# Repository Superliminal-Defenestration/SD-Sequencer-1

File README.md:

Drum machine / sequencer being developed in Kicad 8. Open source and free to use, based mainly on Roland TR808s, etc.
As simple as it gets--- nothing to produce fancy attack/decay envelopes on most stuff, mostly only fancy VCA envelopes for white-noise based sounds. This is meant to be as easy to understand and low-cost as possible.
I'll be writing in notes as I develop the system on what math I'm using to determine components :).

White noise generation with transistor breakdown accredited to Moritz Klein!

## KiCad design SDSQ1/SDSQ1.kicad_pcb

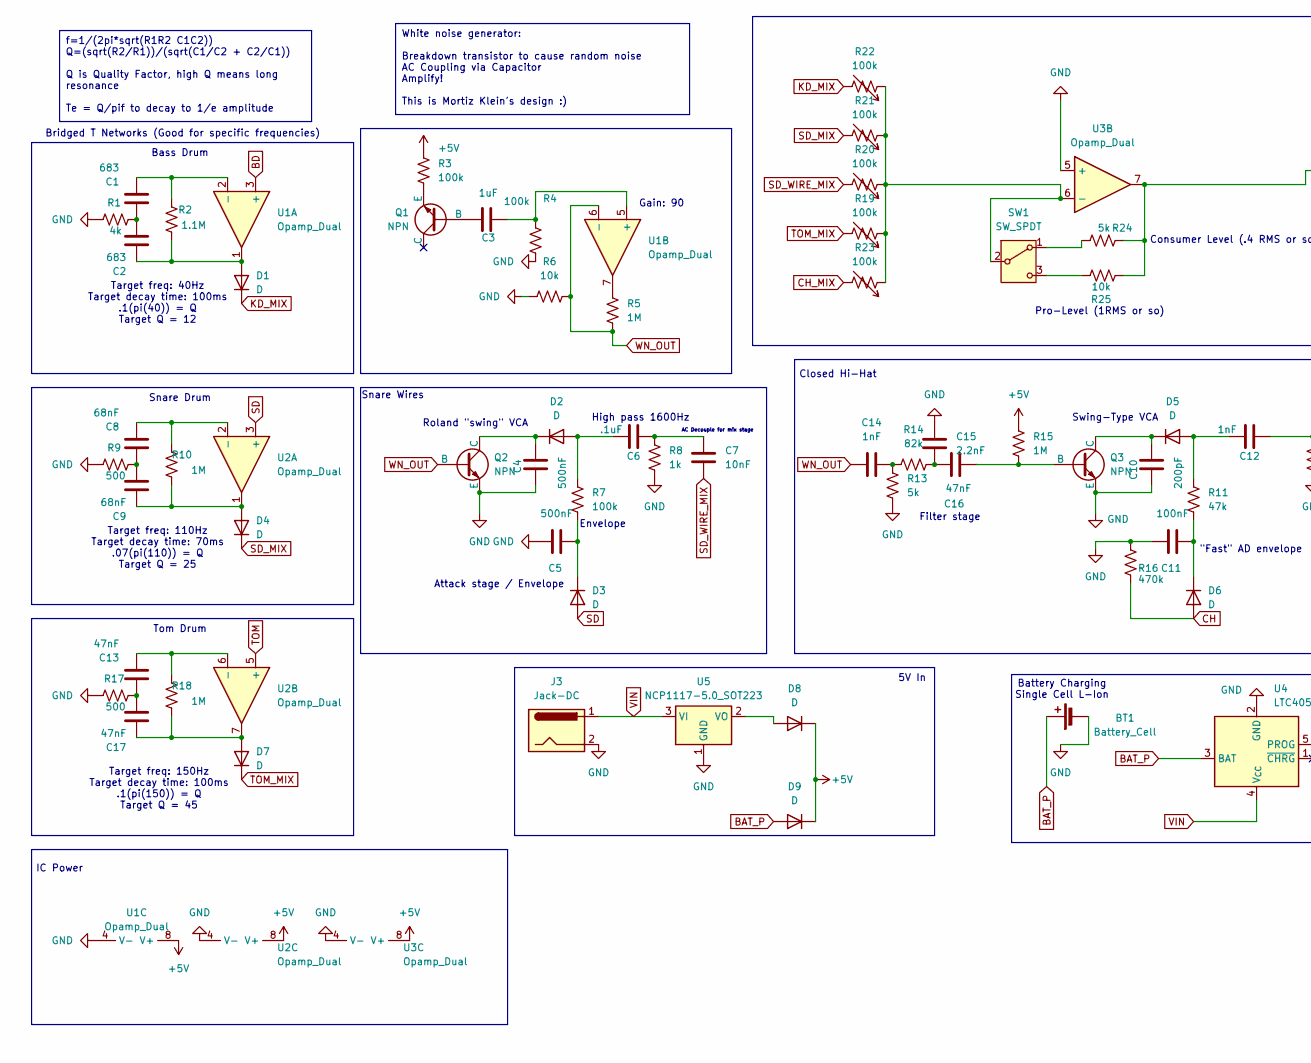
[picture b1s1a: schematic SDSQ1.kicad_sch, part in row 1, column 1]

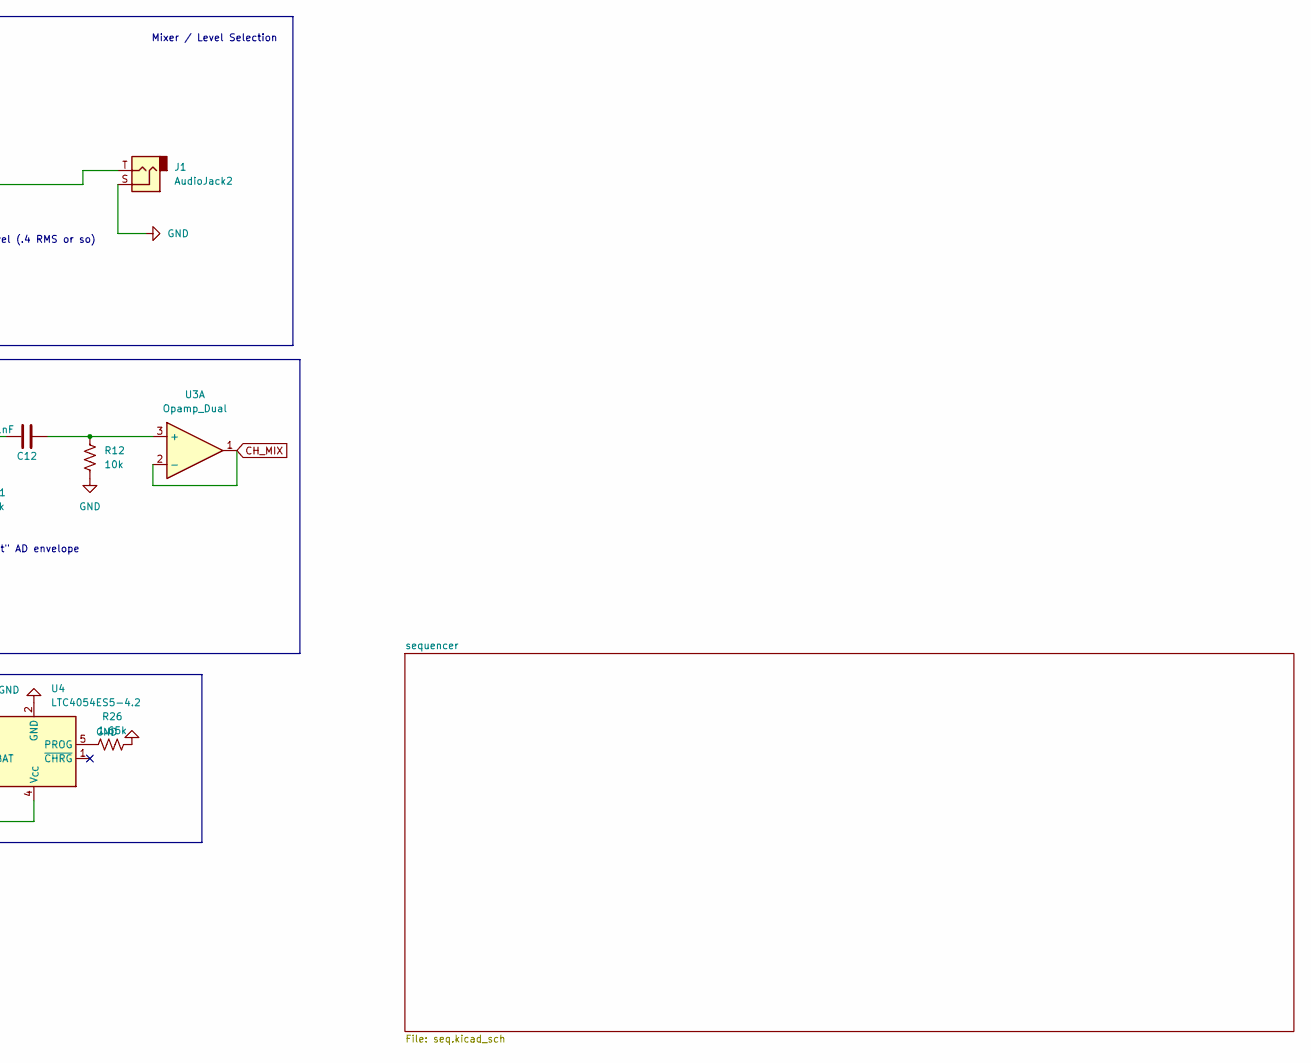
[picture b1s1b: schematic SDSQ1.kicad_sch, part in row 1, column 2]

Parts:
BT1: Battery_Cell; BatteryHolder_Keystone_1042_1x18650
C1, C2: 683; C_Axial_L3.8mm_D2.6mm_P7.50mm_Horizontal
C3: 1uF; C_Axial_L3.8mm_D2.6mm_P7.50mm_Horizontal
C4, C5: 500nF; C_Axial_L3.8mm_D2.6mm_P7.50mm_Horizontal
C6: .1uF; C_Axial_L3.8mm_D2.6mm_P7.50mm_Horizontal
C7: 10nF; C_Axial_L3.8mm_D2.6mm_P7.50mm_Horizontal
C8, C9: 68nF; C_Axial_L3.8mm_D2.6mm_P7.50mm_Horizontal
C10: 200pF; C_Axial_L3.8mm_D2.6mm_P7.50mm_Horizontal
C11: 100nF; C_Axial_L3.8mm_D2.6mm_P7.50mm_Horizontal
C12, C14: 1nF; C_Axial_L3.8mm_D2.6mm_P7.50mm_Horizontal
C13, C16, C17: 47nF; C_Axial_L3.8mm_D2.6mm_P7.50mm_Horizontal
C15: 2.2nF; C_Axial_L3.8mm_D2.6mm_P7.50mm_Horizontal
D1, D2, D3, D4, D5, D6, D7, D8, D9: D; D_A-405_P7.62mm_Horizontal
J1: AudioJack2; Jack_3.5mm_PJ320E_Horizontal
J3: Jack-DC; BarrelJack_Horizontal
Q1, Q2, Q3: NPN; TO-92S
R1: 4k; R_Axial_DIN0204_L3.6mm_D1.6mm_P5.08mm_Vertical
R2: 1.1M; R_Axial_DIN0204_L3.6mm_D1.6mm_P5.08mm_Vertical
R3, R4, R7, R19, R20, R21, R22, R23: 100k; R_Axial_DIN0204_L3.6mm_D1.6mm_P5.08mm_Vertical
R5, R10, R15, R18: 1M; R_Axial_DIN0204_L3.6mm_D1.6mm_P5.08mm_Vertical
R6, R12, R25: 10k; R_Axial_DIN0204_L3.6mm_D1.6mm_P5.08mm_Vertical
R8: 1k; R_Axial_DIN0204_L3.6mm_D1.6mm_P5.08mm_Vertical
R9, R17: 500; R_Axial_DIN0204_L3.6mm_D1.6mm_P5.08mm_Vertical
R11: 47k; R_Axial_DIN0204_L3.6mm_D1.6mm_P5.08mm_Vertical
R13, R24: 5k; R_Axial_DIN0204_L3.6mm_D1.6mm_P5.08mm_Vertical
R14: 82k; R_Axial_DIN0204_L3.6mm_D1.6mm_P5.08mm_Vertical
R16: 470k; R_Axial_DIN0204_L3.6mm_D1.6mm_P5.08mm_Vertical
R26: 1.65k; R_Axial_DIN0204_L3.6mm_D1.6mm_P5.08mm_Vertical
SW1: SW_SPDT; SW_Push_1P2T_Vertical_E-Switch_800UDP8P1A1M6
U1, U2, U3: Opamp_Dual; DIP-8_W7.62mm_Socket
U4: LTC4054ES5-4.2; TSOT-23-5
U5: NCP1117-5.0_SOT223; SOT-223-3_TabPin2

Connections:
+5V: D8.1 (K), D9.1 (K), R3.1, R15.1, U1.8 (V+), U2.8 (V+), U3.8 (V+); also elsewhere on the board
BAT_P: BT1.1 (+), D9.2 (A), U4.3 (BAT)
BD: U1.3 (+); also elsewhere on the board
CH: D6.2 (A), R16.2; also elsewhere on the board
CH_MIX: R23.2, U3.1, U3.2 (-)
GND: BT1.2 (-), C4.2, C5.1, C10.2, C11.1, C15.2, J1.S, J3.2, Q2.3 (E), Q3.3 (E), R1.1, R4.2, R6.1, R8.2, R9.1, R12.2, R13.2, R16.1, R17.1, R26.2, U1.4 (V-), U2.4 (V-), U3.4 (V-), U3.5 (+), U4.2 (GND), U5.1 (GND); also elsewhere on the board
KD_MIX: D1.1 (K), R22.2
unnamed: C1.2, C2.1, R1.2
unnamed: C6.2, C7.2, R8.1
unnamed: C8.2, C9.1, R9.2
unnamed: C13.2, C17.1, R17.2
unnamed: C14.2, R13.1, R14.1
unnamed: C15.1, C16.2, R14.2
unnamed: C2.2, D1.2 (A), R2.1, U1.1
unnamed: C6.1, D2.2 (A), R7.1
unnamed: C4.1, D2.1 (K), Q2.1 (C)
unnamed: C5.2, D3.1 (K), R7.2
unnamed: C9.2, D4.2 (A), R10.1, U2.1
unnamed: C12.1, D5.2 (A), R11.1
unnamed: C10.1, D5.1 (K), Q3.1 (C)
unnamed: C11.2, D6.1 (K), R11.2
unnamed: C17.2, D7.2 (A), R18.1, U2.7
unnamed: D8.2 (A), U5.2 (VO)
unnamed: J1.T, R24.2, R25.2, U3.7
unnamed: C3.1, Q1.2 (B)
unnamed: Q1.3 (E), R3.2
unnamed: C16.1, Q3.2 (B), R15.2
unnamed: R5.1, U1.7
unnamed: R24.1, SW1.1 (A)
unnamed: R19.1, R20.1, R21.1, R22.1, R23.1, SW1.2 (B), U3.6 (-)
unnamed: R25.1, SW1.3 (C)
unnamed: C1.1, R2.2, U1.2 (-)
unnamed: C3.2, R4.1, U1.5 (+)
unnamed: C8.1, R10.2, U2.2 (-)
unnamed: C13.1, R18.2, U2.6 (-)
unnamed: C12.2, R12.1, U3.3 (+)
unnamed: R26.1, U4.5 (PROG)
SD: D3.2 (A), U2.3 (+); also elsewhere on the board
SD_MIX: D4.1 (K), R21.2
SD_WIRE_MIX: C7.1, R20.2
TOM: U2.5 (+); also elsewhere on the board
TOM_MIX: D7.1 (K), R19.2
VIN: J3.1, U4.4 (V_{CC}), U5.3 (VI)
WN_OUT: C14.1, Q2.2 (B), R5.2, R6.2, U1.6 (-)

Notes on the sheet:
White noise generator: Breakdown transistor to cause random noise AC Coupling via Capacitor Amplify! This is Mortiz Klein's design :)
f=1/(2pi*sqrt(R1R2 C1C2)) Q=(sqrt(R2/R1))/(sqrt(C1/C2 + C2/C1)) Q is Quality Factor, high Q means long resonance Te = Q/pif to decay to 1/e amplitude
Envelope
"Fast" AD envelope
Closed Hi-Hat
Swing-Type VCA
AC Decouple for mix stage
5V In
Snare Drum
Bridged T Networks (Good for specific frequencies)
Target freq: 110Hz Target decay time: 70ms .07(pi(110)) = Q Target Q = 25
IC Power
Mixer / Level Selection
Roland "swing" VCA
Tom Drum
Snare Wires
Target freq: 40Hz Target decay time: 100ms .1(pi(40)) = Q Target Q = 12
Battery Charging Single Cell L-Ion
Pro-Level (1RMS or so)
High pass 1600Hz
Consumer Level (.4 RMS or so)
Filter stage
Gain: 90
Bass Drum
Attack stage / Envelope
Target freq: 150Hz Target decay time: 100ms .1(pi(150)) = Q Target Q = 45

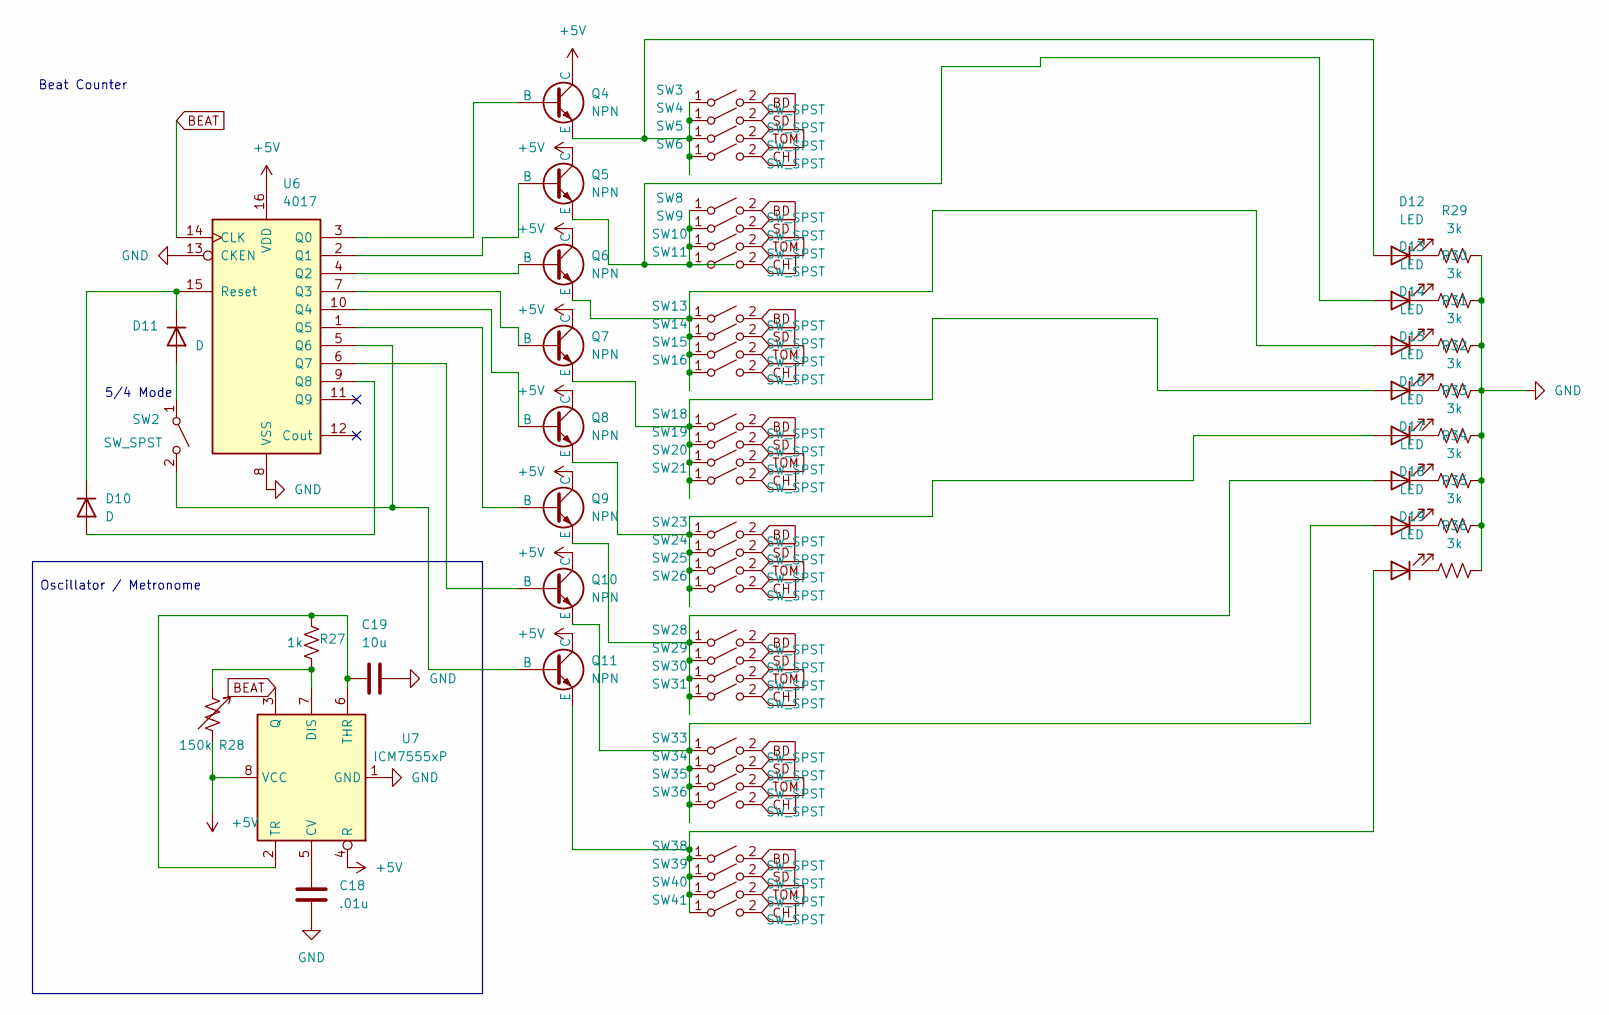
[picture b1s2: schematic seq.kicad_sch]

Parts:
C18: .01u; C_Axial_L3.8mm_D2.6mm_P7.50mm_Horizontal
C19: 10u; C_Axial_L3.8mm_D2.6mm_P7.50mm_Horizontal
D10, D11: D; D_A-405_P7.62mm_Horizontal
D12, D13, D14, D15, D16, D17, D18, D19: LED; LED_D3.0mm
Q4, Q5, Q6, Q7, Q8, Q9, Q10, Q11: NPN; TO-92
R27: 1k; R_Axial_DIN0204_L3.6mm_D1.6mm_P5.08mm_Vertical
R28: 150k; Potentiometer_Bourns_PTV09A-1_Single_Vertical
R29, R30, R31, R32, R33, R34, R35, R36: 3k; R_Axial_DIN0204_L3.6mm_D1.6mm_P5.08mm_Vertical
SW2, SW3, SW4, SW5, SW6, SW8, SW9, SW10, SW11, SW13, SW14, SW15, SW16, SW18, SW19, SW20, SW21, SW23, SW24, SW25, SW26, SW28, SW29, SW30, SW31, SW33, SW34, SW35, SW36, SW38, SW39, SW40, SW41: SW_SPST; SW_CW_GPTS203211B
U6: 4017; DIP-16_W7.62mm_Socket
U7: ICM7555xP; DIP-8_W7.62mm

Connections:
+5V: Q4.1 (C), Q5.1 (C), Q6.1 (C), Q7.1 (C), Q8.1 (C), Q9.1 (C), Q10.1 (C), Q11.1 (C), R28.2, U6.16 (VDD), U7.4 (R), U7.8 (VCC); also elsewhere on the board
BD: SW3.2 (B), SW8.2 (B), SW13.2 (B), SW18.2 (B), SW23.2 (B), SW28.2 (B), SW33.2 (B), SW38.2 (B); also elsewhere on the board
BEAT: U6.14 (CLK), U7.3 (Q)
CH: SW6.2 (B), SW11.2 (B), SW16.2 (B), SW21.2 (B), SW26.2 (B), SW31.2 (B), SW36.2 (B), SW41.2 (B); also elsewhere on the board
GND: C18.2, C19.1, R29.2, R30.2, R31.2, R32.2, R33.2, R34.2, R35.2, R36.2, U6.8 (VSS), U6.13 (CKEN), U7.1 (GND); also elsewhere on the board
unnamed: D10.2 (A), U6.9 (Q8)
unnamed: D10.1 (K), D11.1 (K), U6.15 (Reset)
unnamed: D11.2 (A), SW2.1 (A)
unnamed: D12.2 (A), Q4.3 (E), SW3.1 (A), SW4.1 (A), SW5.1 (A), SW6.1 (A)
unnamed: D12.1 (K), R29.1
unnamed: D13.2 (A), Q5.3 (E), SW8.1 (A), SW9.1 (A), SW10.1 (A), SW11.1 (A)
unnamed: D13.1 (K), R30.1
unnamed: D14.2 (A), Q6.3 (E), SW13.1 (A), SW14.1 (A), SW15.1 (A), SW16.1 (A)
unnamed: D14.1 (K), R31.1
unnamed: D15.2 (A), Q7.3 (E), SW18.1 (A), SW19.1 (A), SW20.1 (A), SW21.1 (A)
unnamed: D15.1 (K), R32.1
unnamed: D16.2 (A), Q8.3 (E), SW23.1 (A), SW24.1 (A), SW25.1 (A), SW26.1 (A)
unnamed: D16.1 (K), R33.1
unnamed: D17.2 (A), Q9.3 (E), SW28.1 (A), SW29.1 (A), SW30.1 (A), SW31.1 (A)
unnamed: D17.1 (K), R34.1
unnamed: D18.2 (A), Q10.3 (E), SW33.1 (A), SW34.1 (A), SW35.1 (A), SW36.1 (A)
unnamed: D18.1 (K), R35.1
unnamed: D19.2 (A), Q11.3 (E), SW38.1 (A), SW39.1 (A), SW40.1 (A), SW41.1 (A)
unnamed: D19.1 (K), R36.1
unnamed: Q4.2 (B), U6.3 (Q0)
unnamed: Q5.2 (B), U6.2 (Q1)
unnamed: Q6.2 (B), U6.4 (Q2)
unnamed: Q7.2 (B), U6.7 (Q3)
unnamed: Q8.2 (B), U6.10 (Q4)
unnamed: Q9.2 (B), U6.1 (Q5)
unnamed: Q10.2 (B), U6.6 (Q7)
unnamed: Q11.2 (B), SW2.2 (B), U6.5 (Q6)
unnamed: C18.1, U7.5 (CV)
unnamed: R27.1, R28.1, U7.7 (DIS)
unnamed: C19.2, R27.2, U7.2 (TR), U7.6 (THR)
SD: SW4.2 (B), SW9.2 (B), SW14.2 (B), SW19.2 (B), SW24.2 (B), SW29.2 (B), SW34.2 (B), SW39.2 (B); also elsewhere on the board
TOM: SW5.2 (B), SW10.2 (B), SW15.2 (B), SW20.2 (B), SW25.2 (B), SW30.2 (B), SW35.2 (B), SW40.2 (B); also elsewhere on the board

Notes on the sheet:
Beat Counter
Oscillator / Metronome
5/4 Mode

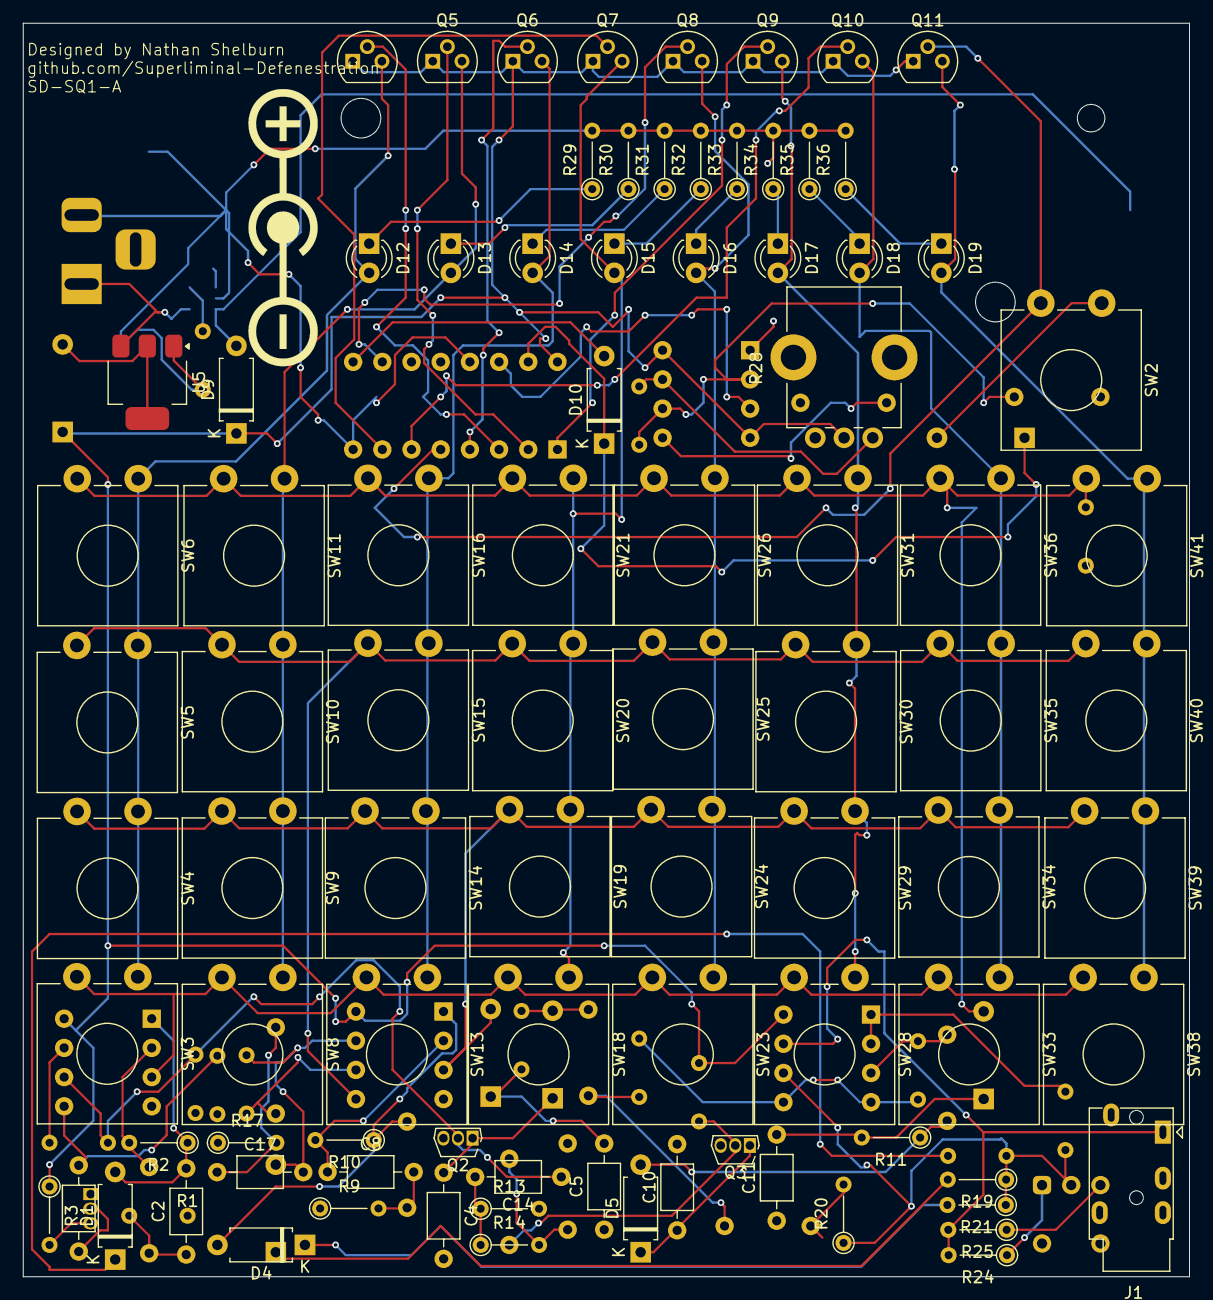
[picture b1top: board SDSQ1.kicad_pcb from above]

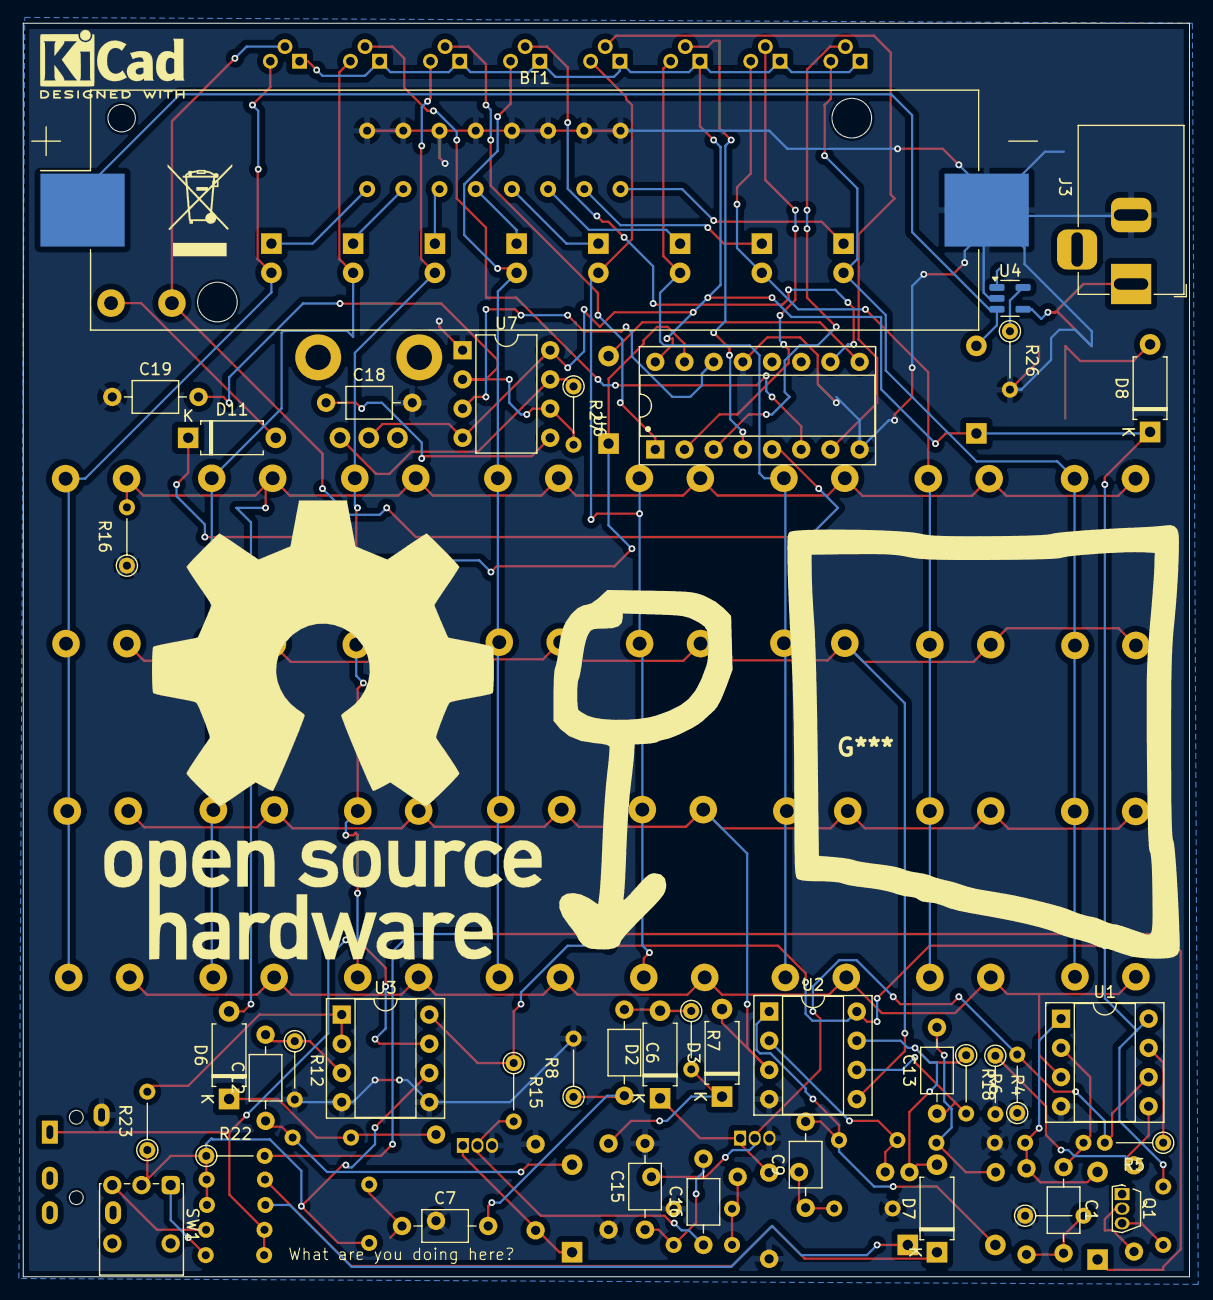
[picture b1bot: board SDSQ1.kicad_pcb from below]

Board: 2 copper layers, 101.5 x 109.1 mm, 129 parts (40 on the bottom side), 75 nets.

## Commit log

2026-03-13 Added bass and WNG
2026-03-13 Create LICENSE
2026-03-13 Add initial project description to README
    Added project description and notes on development.
2026-03-18 added snare wire noise
2026-03-18 snare main drum
2026-04-16 added hats
2026-04-16 added pow management
2026-04-21 fabriacation
2026-04-22 removed ignores
